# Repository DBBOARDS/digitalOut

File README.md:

# digitalOut
These are the Eagle board and schematic files for DB Boards' Digital Out Board

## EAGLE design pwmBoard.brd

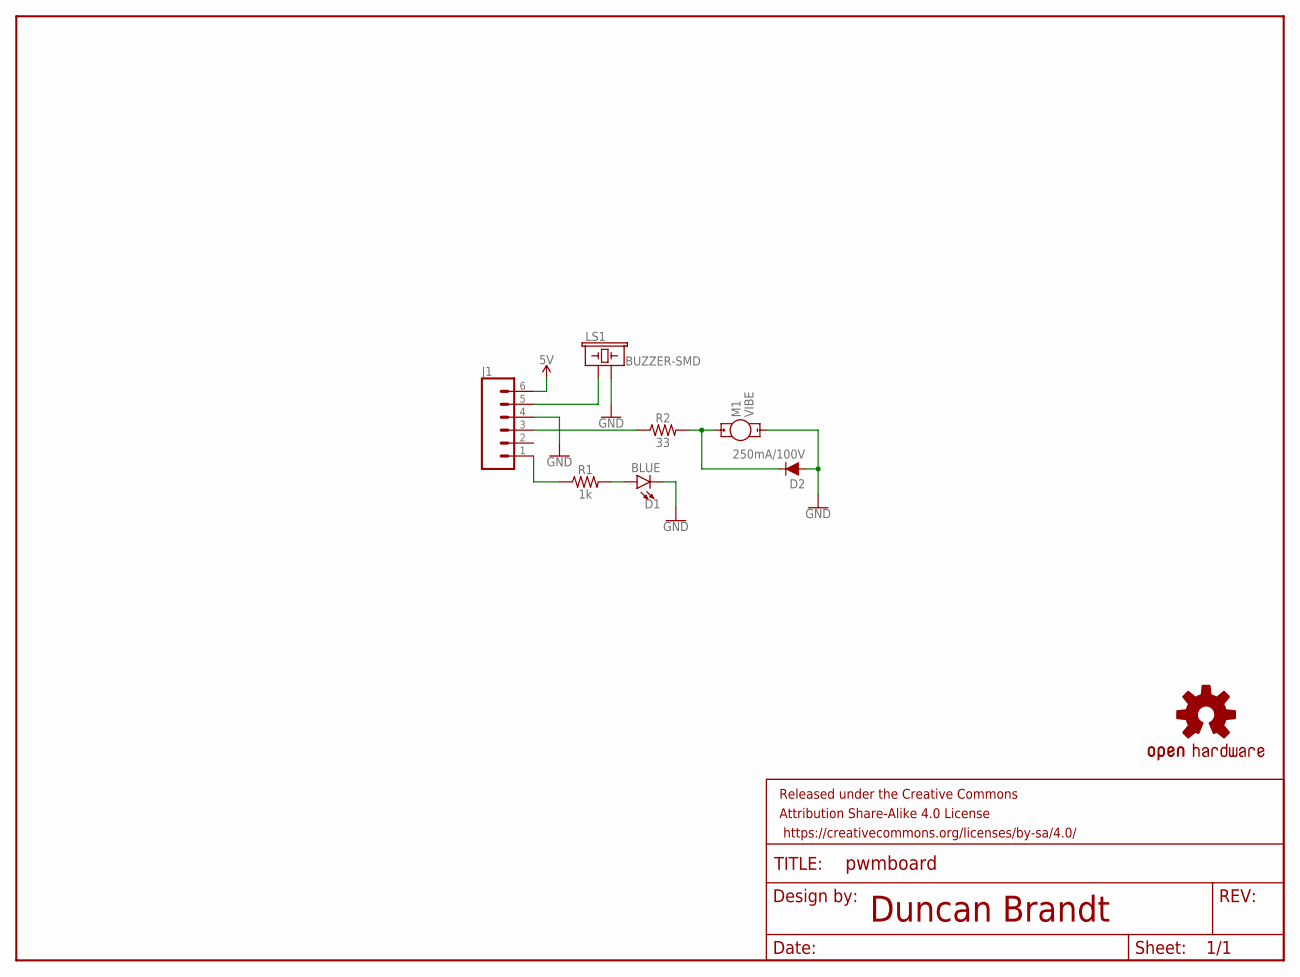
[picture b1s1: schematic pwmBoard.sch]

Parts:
D1: BLUE; LED-1206
D2: 250mA/100V; SOD-323
FRAME1: FRAME-LETTER; CREATIVE_COMMONS
J1: CONN_06SILK_FEMALE_PTH; 1X06
LOGO1: OSHW-LOGOL; OSHW-LOGO-L
LS1: BUZZER-SMD; BUZZER-CCV
M1: VIBE; VIBE-MOTOR-10MM
R1: 1k; 0603
R2: 33; 0603

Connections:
5V: J1.6
GND: D1.C, D2.A, J1.4, LS1.- (2), M1.-
unnamed: J1.1, R1.1
unnamed: D1.A, R1.2
unnamed: D2.C, M1.+, R2.2
unnamed: J1.3, R2.1
unnamed: J1.5, LS1.+ (1)

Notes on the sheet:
Duncan Brandt

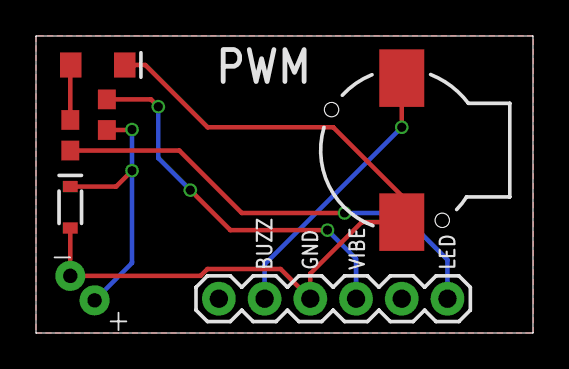
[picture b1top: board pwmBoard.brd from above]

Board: 2 copper layers, 27.6 x 16.5 mm, 9 parts (1 on the bottom side), 6 nets.

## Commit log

2018-01-17 eagle files
    the board is under revision for our educational kit and will be represented here when appropriate

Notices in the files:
parts and their libraries:
DB-LED: Licensing: Creative Commons ShareAlike 4.0 International - https://creativecommons.org/licenses/by-sa/4.0
DB-SYMBOLS: Released under the Creative Commons Attribution Share-Alike 4.0 License
DB-SYMBOLS: https://creativecommons.org/licenses/by-sa/4.0
